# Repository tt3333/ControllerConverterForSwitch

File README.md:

[日本語版 README はこちら](README-ja.md)

# Controller Converter for Switch

Controller Converter for Switch is a converter that allows the following controllers to be used with Nintendo Switch.

* Controller included with SNES
* Controller included with SNES Classic Edition
* Classic Controller for Wii
* Classic Controller PRO for Wii

Inputs are read in 1ms cycles, resulting in almost no input delay.

## How to Use

* Connect any of the above controllers.
* Connect to Nintendo Switch dock with a USB cable.
* You can replace L+R with ZL+ZR by turning on the toggle switch.<BR>
  This is useful when using an SNES controller with Nintendo Switch Online.
* It is possible to use a SNES controller and a Wii controller at the same time.<BR>
  However, pressing left and right or up and down at the same time will be ignored.
* The position of the sticks at the time the connection of the Wii controller is detected is considered neutral.<BR>
  Do not tilt the sticks when plugging in the Wii controller or USB cable.

## How to Build Hardware

### Ordering PCBs

#### If you place an order with JLCPCB and want the order number printed in an inconspicuous location

Upload gerber_JLCPCB.zip and select "Specify a location" from the "Remove Order Number" options.

#### If you place an order with JLCPCB and do not want the order number printed

Upload gerber.zip and select "Yes" from the "Remove Order Number" options.<BR>
However, if Yes is selected, an optional fee will be charged.

#### For orders outside of JLCPCB

Upload gerber.zip.

### Selection of Level Converter

SNES controller operates at 5V, but Raspberry Pi Pico operates at 3.3V.<BR>
Therefore, when using SNES controller, a level converter is required to convert between 5V and 3.3V.

* AE-LCNV4-MOSFET manufactured by Akizuki Denshi Tsusho has been tested.<BR>
  If you use AE-LCNV4-MOSFET, mount it with the side with the pin names facing up.
* BOB-12009 manufactured by SparkFun should also work because it is exactly the same circuit as AE-LCNV4-MOSFET.<BR>
  If you use BOB-12009, mount it with the side with chips facing up.<BR>
  (The numbers on the pin names are in reverse order from the AE-LCNV4-MOSFET.)
* There are several level converters on Amazon that have the same pin layout as BOB-12009,
  but there is no guarantee that they will work exactly the same way because the chips they contain are unknown.

### Selection of Case

The PCB is designed for the following cases.

* PR-105B manufactured by TAKACHI ELECTRONICS ENCLOSURE
* PR-105G manufactured by TAKACHI ELECTRONICS ENCLOSURE
* TB-32-B manufactured by Teishin Electric
* TB-32-IV manufactured by Teishin Electric

Make holes for USB connector, toggle switch, and controller cables.

### Assembly

* Solder sockets to U1 and mount a Raspberry Pi Pico.
* Solder sockets to U2 and mount a level converter.
* Connect a toggle switch to SW1.
* A reset switch can be attached to SW2, but there is no problem even without it.
* Cut the extension cable for Wii in half and connect the female cable to CN1.
* Cut the extension cable for SNES in half and connect the female cable to CN2.
* CN3 and TP1 are for debugging firmware, so normally nothing needs to be connected.
* While pressing the BOOTSEL button on the Raspberry Pi Pico, connect the USB cable and write the firmware.ino.uf2.

## If you modify firmware

* If you connect a USB serial converter to CN3 and enable `#define DEBUG` in firmware.ino, debug output is available.<BR>
  However, when using the debug output, it will not be possible to read the input in 1 ms cycles.
* If you connect an oscilloscope to TP1, you can check whether input is read within 1ms.<BR>
  (TP1 goes high while reading Wii controller.)

### How to Build Firmware

1. Install Arduino IDE
2. Open firmware.ino
3. Click "File", then "Preferences..."
4. Copy and paste the following URL into the "Additional boards manager URLs" field and click "OK"<BR>
   `https://github.com/earlephilhower/arduino-pico/releases/download/global/package_rp2040_index.json`
5. Click "Tools", "Board", then "Board Manager..."
6. Type "pico" in the search field and install "Raspberry Pi Pico/RP2040 by Earle F. Philhower, III"
7. Click "Tools", "Board", "Raspberry Pi Pico/RP2040", then "Raspberry Pi Pico"
8. Click "Tools", "Optimize", then "Fast (-Ofast) (maybe slower)"
9. Click "Tools", "USB Stack", then "No USB"
10. Click "Sketch", then "Export Compiled Binary"

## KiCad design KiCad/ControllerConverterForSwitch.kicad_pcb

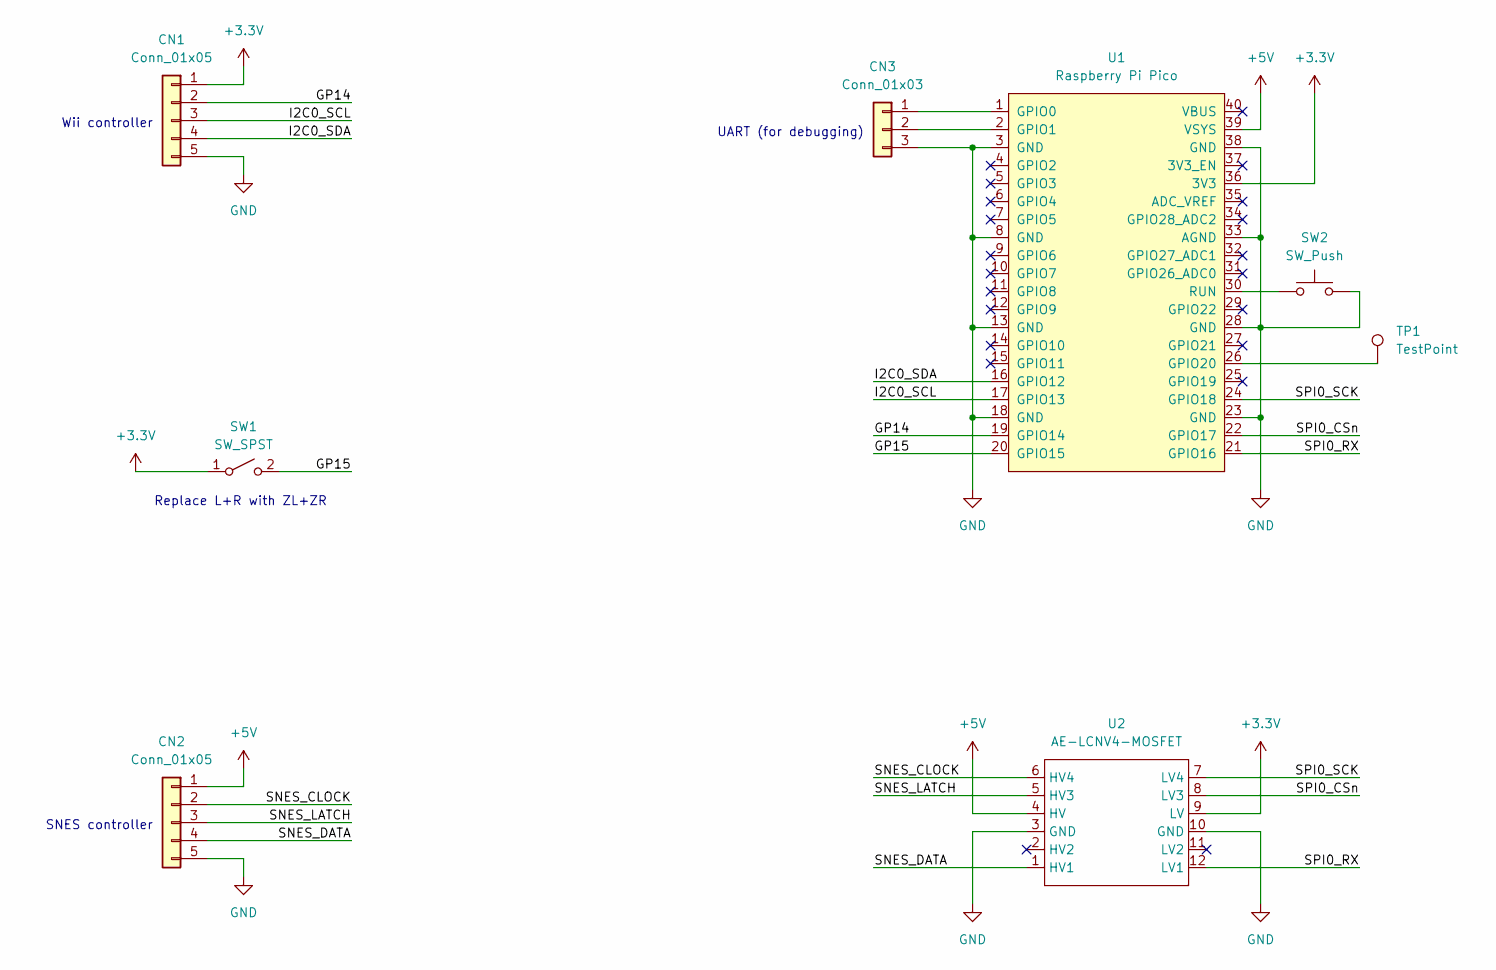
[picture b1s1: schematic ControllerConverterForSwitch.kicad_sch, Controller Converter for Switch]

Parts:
CN1, CN2: Conn_01x05; PinHeader_1x05_P2.54mm_Vertical
CN3: Conn_01x03; PinHeader_1x03_P2.54mm_Vertical
SW1: SW_SPST; PinHeader_1x02_P2.54mm_Vertical
SW2: SW_Push; SW_PUSH_6mm
TP1: TestPoint; TestPoint_THTPad_D1.7mm_Drill1.0mm
U1: Raspberry Pi Pico; RPi_Pico_SMD_TH
U2: AE-LCNV4-MOSFET

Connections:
+3.3V: CN1.1, SW1.1 (A), U1.36 (3V3), U2.9 (LV)
+5V: CN2.1, U1.39 (VSYS), U2.4 (HV)
/GP14: CN1.2, U1.19 (GPIO14)
/GP15: SW1.2 (B), U1.20 (GPIO15)
/I2C0_SCL: CN1.3, U1.17 (GPIO13)
/I2C0_SDA: CN1.4, U1.16 (GPIO12)
/SNES_CLOCK: CN2.2, U2.6 (HV4)
/SNES_DATA: CN2.4, U2.1 (HV1)
/SNES_LATCH: CN2.3, U2.5 (HV3)
/SPI0_CSn: U1.22 (GPIO17), U2.8 (LV3)
/SPI0_RX: U1.21 (GPIO16), U2.12 (LV1)
/SPI0_SCK: U1.24 (GPIO18), U2.7 (LV4)
GND: CN1.5, CN2.5, CN3.3, SW2.2, U1.3 (GND), U1.8 (GND), U1.13 (GND), U1.18 (GND), U1.23 (GND), U1.28 (GND), U1.33 (AGND), U1.38 (GND), U2.3 (GND), U2.10 (GND)
unnamed: CN3.1, U1.1 (GPIO0)
unnamed: CN3.2, U1.2 (GPIO1)
unnamed: SW2.1, U1.30 (RUN)
unnamed: TP1.1, U1.26 (GPIO20)

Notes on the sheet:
UART (for debugging)
Wii controller
Replace L+R with ZL+ZR
SNES controller

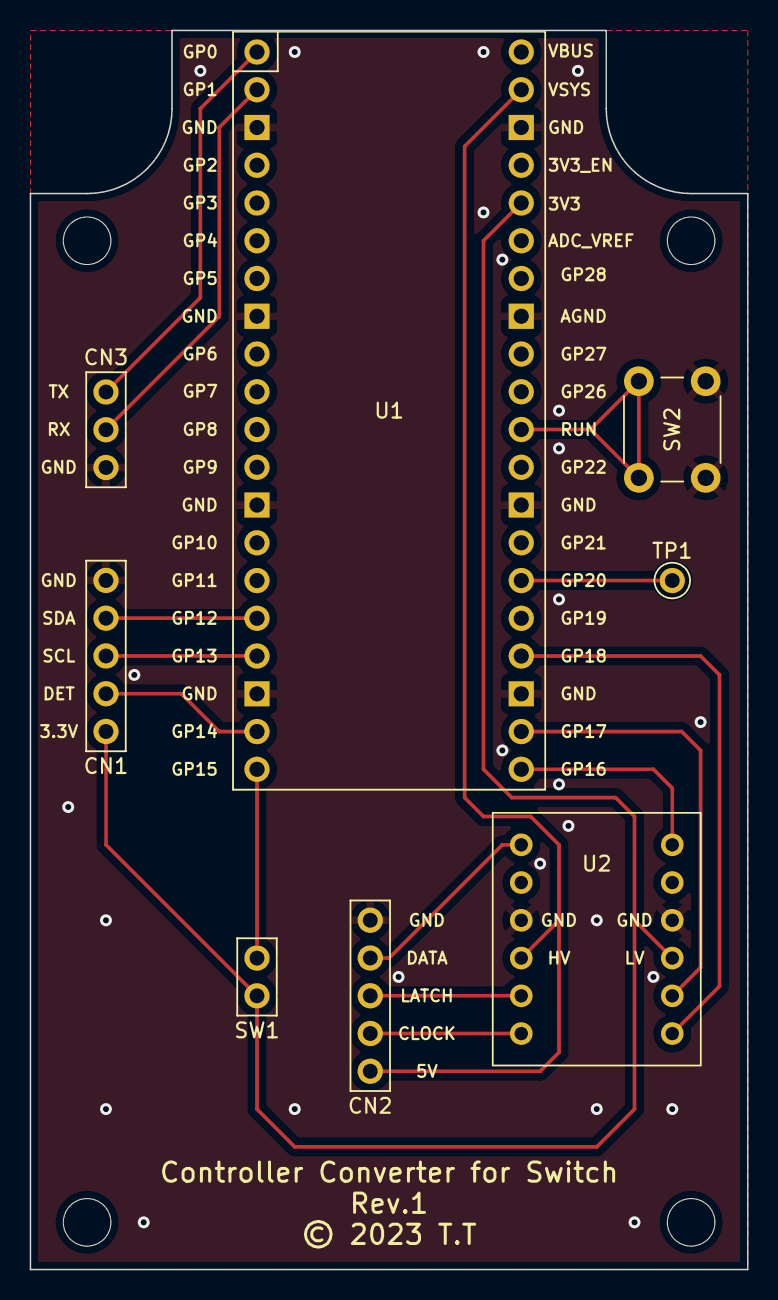
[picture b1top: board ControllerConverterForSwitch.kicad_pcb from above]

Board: 2 copper layers, 48.3 x 83.4 mm, 8 parts (0 on the bottom side), 17 nets.

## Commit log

2023-02-05 add LICENSE
2023-02-05 add .gitignore
2023-02-05 add firmware project
2023-02-05 add schematic.pdf
2023-02-05 add firmware binary
2023-02-05 add JLCJLCJLCJLC
2023-02-05 add KiCad project
2023-02-05 add gerber file
2023-02-05 add README
2024-02-10 add calibration
    The position of the sticks at the time the connection of the Wii controller is detected is considered neutral.
2024-03-24 Corrected a typo in the README

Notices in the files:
KiCad/ControllerConverterForSwitch.kicad_pcb:
© 2023 T.T
